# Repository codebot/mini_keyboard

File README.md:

# mini_keyboard

 * mk1: based on Cherry ML. Unfinished
 * mk2: based on Kailh 1350 low-profile "Choc"

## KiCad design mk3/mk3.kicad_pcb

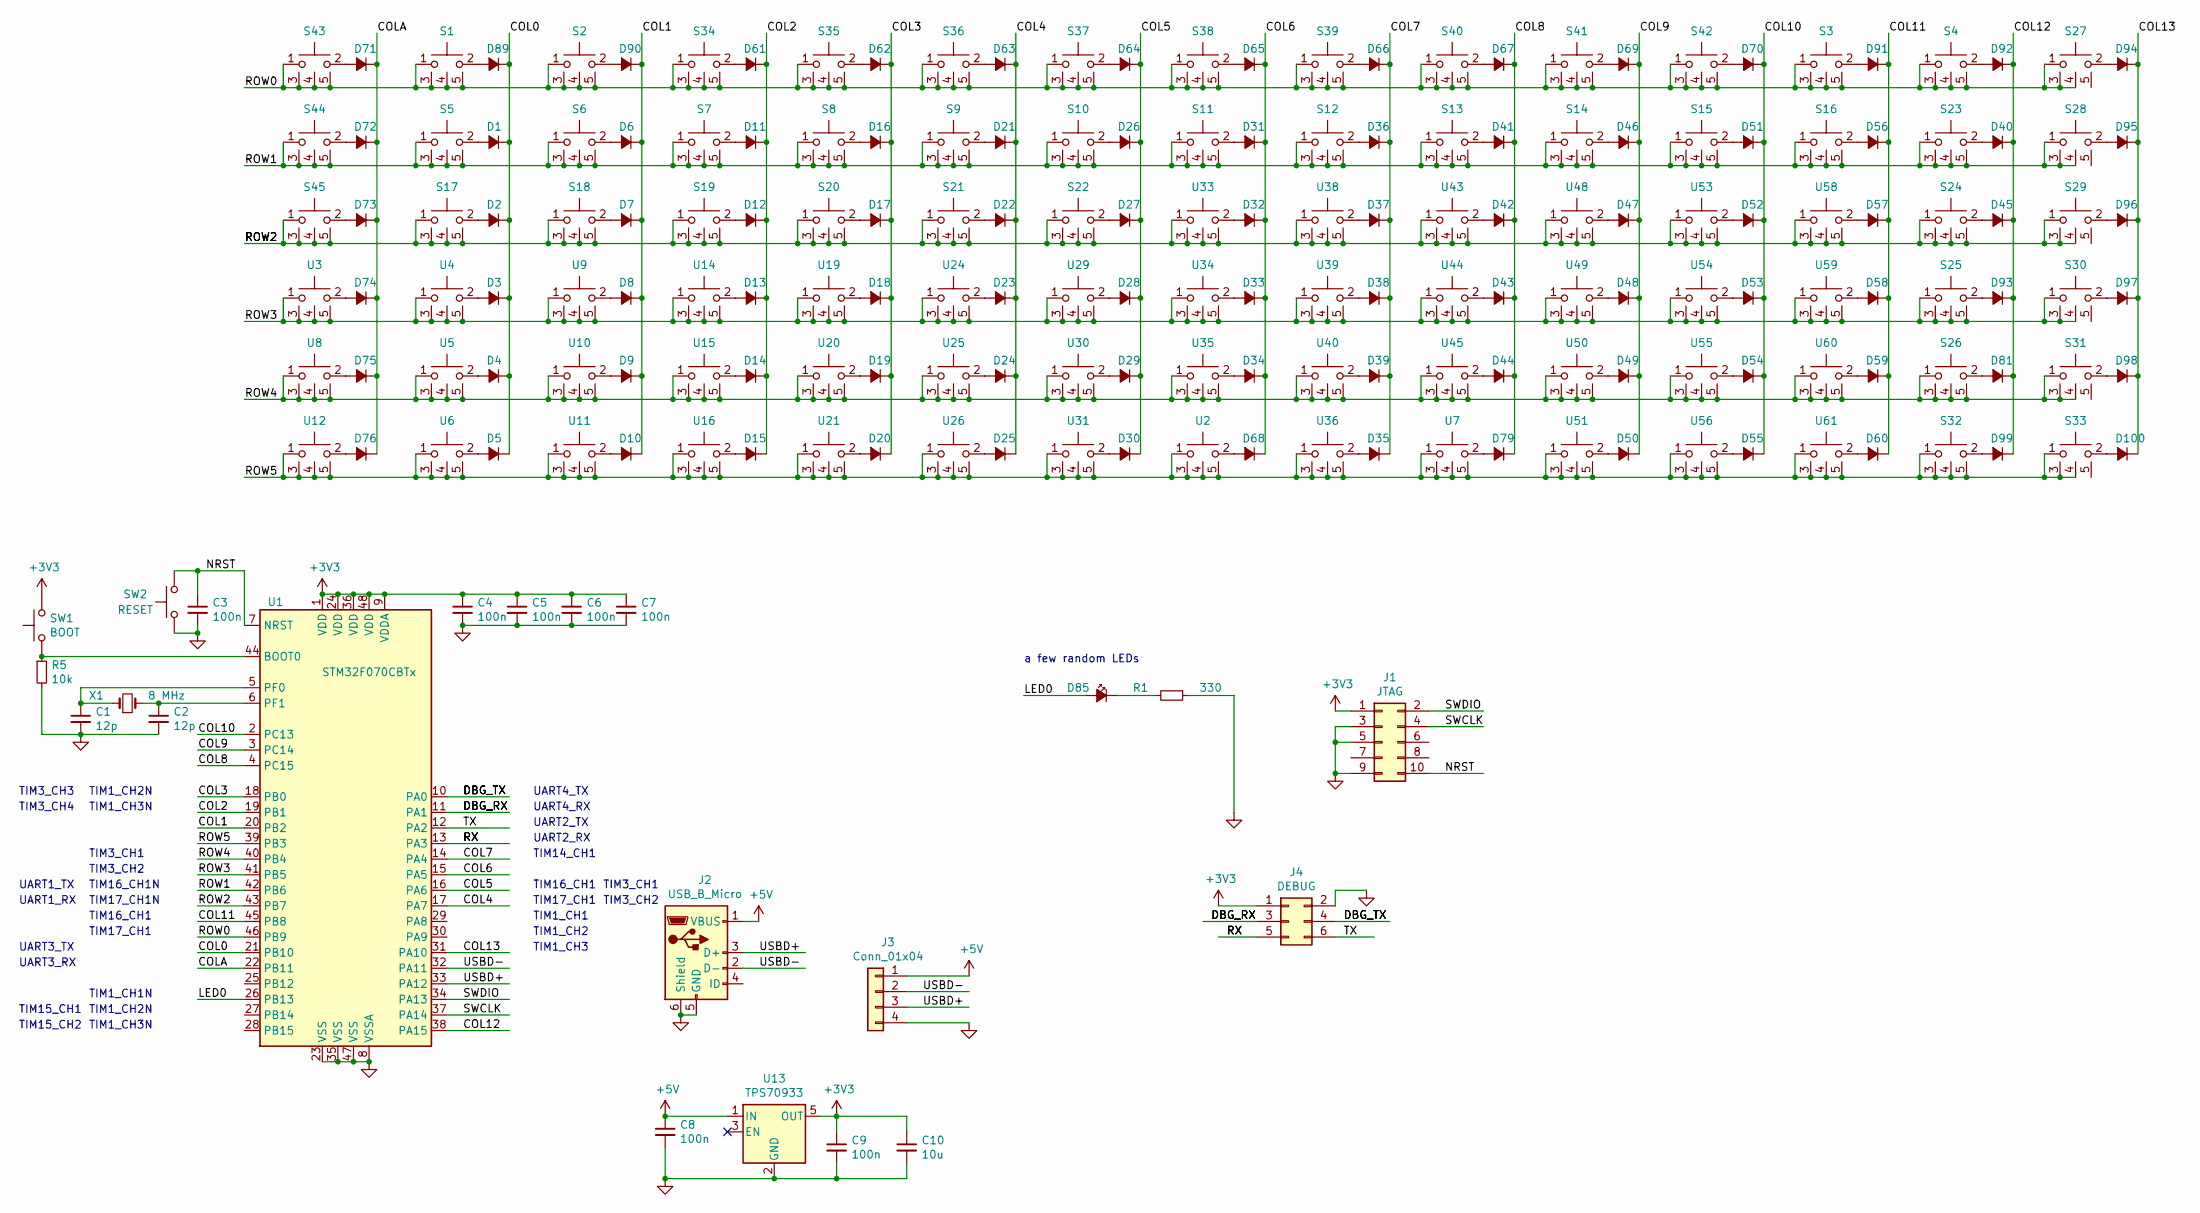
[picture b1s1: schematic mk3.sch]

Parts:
C1, C2: 12p; C_0603_1608Metric
C3, C4, C5, C6, C7, C8, C9: 100n; C_0603_1608Metric
C10: 10u; C_0805_2012Metric
D1, D2, D3, D4, D5, D6, D7, D8, D9, D10, D11, D12, D13, D14, D15, D16, D17, D18, D19, D20, D21, D22, D23, D24, D25, D26, D27, D28, D29, D30, D31, D32, D33, D34, D35, D36, D37, D38, D39, D40, D41, D42, D43, D44, D45, D46, D47, D48, D49, D50, D51, D52, D53, D54, D55, D56, D57, D58, D59, D60, D61, D62, D63, D64, D65, D66, D67, D68, D69, D70, D71, D72, D73, D74, D75, D76, D79, D81, D89, D90, D91, D92, D93, D94, D95, D96, D97, D98, D99, D100: 1N4148; D_SOD-123
D85: LED_Small_ALT; LED_D3.0mm
J1: JTAG; PinHeader_2x05_P1.27mm_Vertical
J2: USB_B_Micro; USB_Micro-B_Molex-105017-0001
J3: Conn_01x04; PinHeader_1x04_P2.54mm_Vertical
J4: DEBUG; PinHeader_2x03_P2.54mm_Vertical
R1: 330; R_0603_1608Metric
R5: 10k; R_0603_1608Metric
S1, S2, S3, S4, S5, S6, S7, S8, S9, S10, S11, S12, S13, S14, S15, S16, S17, S18, S19, S20, S21, S22, S23, S24, S25, S26, S27, S28, S29, S30, S31, S32, S33, S34, S35, S36, S37, S38, S39, S40, S41, S42, S43, S44, S45: CHERRY_ML; KAILH_1350
SW1: BOOT; SW_SPST_B3U-1000P
SW2: RESET; SW_SPST_B3U-1000P
U1: STM32F070CBTx; LQFP-48_7x7mm_P0.5mm
U2, U3, U4, U5, U6, U7, U8, U9, U10, U11, U12, U14, U15, U16, U19, U20, U21, U24, U25, U26, U29, U30, U31, U33, U34, U35, U36, U38, U39, U40, U43, U44, U45, U48, U49, U50, U51, U53, U54, U55, U56, U58, U59, U60, U61: CHERRY_ML; KAILH_1350
U13: TPS70933; SOT-23-5
X1: 8 MHz; Crystal_SMD_5032-2Pin_5.0x3.2mm

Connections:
+3V3: C4.1, C5.1, C6.1, C7.1, C9.1, C10.1, J1.1, J4.1, SW1.2, U1.1 (VDD), U1.9 (VDDA), U1.24 (VDD), U1.36 (VDD), U1.48 (VDD), U13.5 (OUT)
+5V: C8.1, J2.1 (VBUS), J3.1, U13.1 (IN)
/COL0: D1.1 (K), D2.1 (K), D3.1 (K), D4.1 (K), D5.1 (K), D89.1 (K), U1.21 (PB10)
/COL1: D6.1 (K), D7.1 (K), D8.1 (K), D9.1 (K), D10.1 (K), D90.1 (K), U1.20 (PB2)
/COL2: D11.1 (K), D12.1 (K), D13.1 (K), D14.1 (K), D15.1 (K), D61.1 (K), U1.19 (PB1)
/COL3: D16.1 (K), D17.1 (K), D18.1 (K), D19.1 (K), D20.1 (K), D62.1 (K), U1.18 (PB0)
/COL4: D21.1 (K), D22.1 (K), D23.1 (K), D24.1 (K), D25.1 (K), D63.1 (K), U1.17 (PA7)
/COL5: D26.1 (K), D27.1 (K), D28.1 (K), D29.1 (K), D30.1 (K), D64.1 (K), U1.16 (PA6)
/COL6: D31.1 (K), D32.1 (K), D33.1 (K), D34.1 (K), D65.1 (K), D68.1 (K), U1.15 (PA5)
/COL7: D35.1 (K), D36.1 (K), D37.1 (K), D38.1 (K), D39.1 (K), D66.1 (K), U1.14 (PA4)
/COL8: D41.1 (K), D42.1 (K), D43.1 (K), D44.1 (K), D67.1 (K), D79.1 (K), U1.4 (PC15)
/COL9: D46.1 (K), D47.1 (K), D48.1 (K), D49.1 (K), D50.1 (K), D69.1 (K), U1.3 (PC14)
/COL10: D51.1 (K), D52.1 (K), D53.1 (K), D54.1 (K), D55.1 (K), D70.1 (K), U1.2 (PC13)
/COL11: D56.1 (K), D57.1 (K), D58.1 (K), D59.1 (K), D60.1 (K), D91.1 (K), U1.45 (PB8)
/COL12: D40.1 (K), D45.1 (K), D81.1 (K), D92.1 (K), D93.1 (K), D99.1 (K), U1.38 (PA15)
/COL13: D94.1 (K), D95.1 (K), D96.1 (K), D97.1 (K), D98.1 (K), D100.1 (K), U1.31 (PA10)
/COLA: D71.1 (K), D72.1 (K), D73.1 (K), D74.1 (K), D75.1 (K), D76.1 (K), U1.22 (PB11)
/DBG_RX: J4.3, U1.11 (PA1)
/DBG_TX: J4.4, U1.10 (PA0)
/LED0: D85.2 (A), U1.26 (PB13)
/NRST: C3.1, J1.10, SW2.2, U1.7 (NRST)
/ROW0: S1.1, S1.3, S1.4, S1.5, S2.1, S2.3, S2.4, S2.5, S3.1, S3.3, S3.4, S3.5, S4.1, S4.3, S4.4, S4.5, S27.1, S27.3, S27.4, S34.1, S34.3, S34.4, S34.5, S35.1, S35.3, S35.4, S35.5, S36.1, S36.3, S36.4, S36.5, S37.1, S37.3, S37.4, S37.5, S38.1, S38.3, S38.4, S38.5, S39.1, S39.3, S39.4, S39.5, S40.1, S40.3, S40.4, S40.5, S41.1, S41.3, S41.4, S41.5, S42.1, S42.3, S42.4, S42.5, S43.1, S43.3, S43.4, S43.5, U1.46 (PB9)
/ROW1: S5.1, S5.3, S5.4, S5.5, S6.1, S6.3, S6.4, S6.5, S7.1, S7.3, S7.4, S7.5, S8.1, S8.3, S8.4, S8.5, S9.1, S9.3, S9.4, S9.5, S10.1, S10.3, S10.4, S10.5, S11.1, S11.3, S11.4, S11.5, S12.1, S12.3, S12.4, S12.5, S13.1, S13.3, S13.4, S13.5, S14.1, S14.3, S14.4, S14.5, S15.1, S15.3, S15.4, S15.5, S16.1, S16.3, S16.4, S16.5, S23.1, S23.3, S23.4, S23.5, S28.1, S28.3, S28.4, S44.1, S44.3, S44.4, S44.5, U1.42 (PB6)
/ROW2: S17.1, S17.3, S17.4, S17.5, S18.1, S18.3, S18.4, S18.5, S19.1, S19.3, S19.4, S19.5, S20.1, S20.3, S20.4, S20.5, S21.1, S21.3, S21.4, S21.5, S22.1, S22.3, S22.4, S22.5, S24.1, S24.3, S24.4, S24.5, S29.1, S29.3, S29.4, S45.1, S45.3, S45.4, S45.5, U1.43 (PB7), U33.1, U33.3, U33.4, U33.5, U38.1, U38.3, U38.4, U38.5, U43.1, U43.3, U43.4, U43.5, U48.1, U48.3, U48.4, U48.5, U53.1, U53.3, U53.4, U53.5, U58.1, U58.3, U58.4, U58.5
/ROW3: S25.1, S25.3, S25.4, S25.5, S30.1, S30.3, S30.4, U1.41 (PB5), U3.1, U3.3, U3.4, U3.5, U4.1, U4.3, U4.4, U4.5, U9.1, U9.3, U9.4, U9.5, U14.1, U14.3, U14.4, U14.5, U19.1, U19.3, U19.4, U19.5, U24.1, U24.3, U24.4, U24.5, U29.1, U29.3, U29.4, U29.5, U34.1, U34.3, U34.4, U34.5, U39.1, U39.3, U39.4, U39.5, U44.1, U44.3, U44.4, U44.5, U49.1, U49.3, U49.4, U49.5, U54.1, U54.3, U54.4, U54.5, U59.1, U59.3, U59.4, U59.5
/ROW4: S26.1, S26.3, S26.4, S26.5, S31.1, S31.3, S31.4, U1.40 (PB4), U5.1, U5.3, U5.4, U5.5, U8.1, U8.3, U8.4, U8.5, U10.1, U10.3, U10.4, U10.5, U15.1, U15.3, U15.4, U15.5, U20.1, U20.3, U20.4, U20.5, U25.1, U25.3, U25.4, U25.5, U30.1, U30.3, U30.4, U30.5, U35.1, U35.3, U35.4, U35.5, U40.1, U40.3, U40.4, U40.5, U45.1, U45.3, U45.4, U45.5, U50.1, U50.3, U50.4, U50.5, U55.1, U55.3, U55.4, U55.5, U60.1, U60.3, U60.4, U60.5
/ROW5: S32.1, S32.3, S32.4, S32.5, S33.1, S33.3, S33.4, U1.39 (PB3), U2.1, U2.3, U2.4, U2.5, U6.1, U6.3, U6.4, U6.5, U7.1, U7.3, U7.4, U7.5, U11.1, U11.3, U11.4, U11.5, U12.1, U12.3, U12.4, U12.5, U16.1, U16.3, U16.4, U16.5, U21.1, U21.3, U21.4, U21.5, U26.1, U26.3, U26.4, U26.5, U31.1, U31.3, U31.4, U31.5, U36.1, U36.3, U36.4, U36.5, U51.1, U51.3, U51.4, U51.5, U56.1, U56.3, U56.4, U56.5, U61.1, U61.3, U61.4, U61.5
/RX: J4.5, U1.13 (PA3)
/SWCLK: J1.4, U1.37 (PA14)
/SWDIO: J1.2, U1.34 (PA13)
/TX: J4.6, U1.12 (PA2)
/USBD+: J2.3 (D+), J3.3, U1.33 (PA12)
/USBD-: J2.2 (D-), J3.2, U1.32 (PA11)
GND: C1.2, C2.2, C3.2, C4.2, C5.2, C6.2, C7.2, C8.2, C9.2, C10.2, J1.3, J1.5, J1.9, J2.5 (GND), J2.6 (Shield), J3.4, J4.2, R1.1, R5.2, SW2.1, U1.8 (VSSA), U1.23 (VSS), U1.35 (VSS), U1.47 (VSS), U13.2 (GND)
unnamed: C1.1, U1.5 (PF0), X1.1
unnamed: C2.1, U1.6 (PF1), X1.2
unnamed: D1.2 (A), S5.2
unnamed: D2.2 (A), S17.2
unnamed: D3.2 (A), U4.2
unnamed: D4.2 (A), U5.2
unnamed: D5.2 (A), U6.2
unnamed: D6.2 (A), S6.2
unnamed: D7.2 (A), S18.2
unnamed: D8.2 (A), U9.2
unnamed: D9.2 (A), U10.2
unnamed: D10.2 (A), U11.2
unnamed: D11.2 (A), S7.2
unnamed: D12.2 (A), S19.2
unnamed: D13.2 (A), U14.2
unnamed: D14.2 (A), U15.2
unnamed: D15.2 (A), U16.2
unnamed: D16.2 (A), S8.2
unnamed: D17.2 (A), S20.2
unnamed: D18.2 (A), U19.2
unnamed: D19.2 (A), U20.2
unnamed: D20.2 (A), U21.2
unnamed: D21.2 (A), S9.2
unnamed: D22.2 (A), S21.2
unnamed: D23.2 (A), U24.2
unnamed: D24.2 (A), U25.2
unnamed: D25.2 (A), U26.2
unnamed: D26.2 (A), S10.2
unnamed: D27.2 (A), S22.2
unnamed: D28.2 (A), U29.2
unnamed: D29.2 (A), U30.2
unnamed: D30.2 (A), U31.2
unnamed: D31.2 (A), S11.2
unnamed: D32.2 (A), U33.2
unnamed: D33.2 (A), U34.2
unnamed: D34.2 (A), U35.2
unnamed: D35.2 (A), U36.2
unnamed: D36.2 (A), S12.2
unnamed: D37.2 (A), U38.2
unnamed: D38.2 (A), U39.2
unnamed: D39.2 (A), U40.2
unnamed: D40.2 (A), S23.2
unnamed: D41.2 (A), S13.2
unnamed: D42.2 (A), U43.2
unnamed: D43.2 (A), U44.2
unnamed: D44.2 (A), U45.2
unnamed: D45.2 (A), S24.2
unnamed: D46.2 (A), S14.2
unnamed: D47.2 (A), U48.2
unnamed: D48.2 (A), U49.2
unnamed: D49.2 (A), U50.2
unnamed: D50.2 (A), U51.2
unnamed: D51.2 (A), S15.2
unnamed: D52.2 (A), U53.2
unnamed: D53.2 (A), U54.2
unnamed: D54.2 (A), U55.2
unnamed: D55.2 (A), U56.2
unnamed: D56.2 (A), S16.2
unnamed: D57.2 (A), U58.2
unnamed: D58.2 (A), U59.2
unnamed: D59.2 (A), U60.2
unnamed: D60.2 (A), U61.2
unnamed: D61.2 (A), S34.2
unnamed: D62.2 (A), S35.2
unnamed: D63.2 (A), S36.2
unnamed: D64.2 (A), S37.2
unnamed: D65.2 (A), S38.2
unnamed: D66.2 (A), S39.2
unnamed: D67.2 (A), S40.2
unnamed: D68.2 (A), U2.2
unnamed: D69.2 (A), S41.2
unnamed: D70.2 (A), S42.2
unnamed: D71.2 (A), S43.2
unnamed: D72.2 (A), S44.2
unnamed: D73.2 (A), S45.2
unnamed: D74.2 (A), U3.2
unnamed: D75.2 (A), U8.2
unnamed: D76.2 (A), U12.2
unnamed: D79.2 (A), U7.2
unnamed: D81.2 (A), S26.2
unnamed: D85.1 (K), R1.2
unnamed: D89.2 (A), S1.2
unnamed: D90.2 (A), S2.2
unnamed: D91.2 (A), S3.2
unnamed: D92.2 (A), S4.2
unnamed: D93.2 (A), S25.2
unnamed: D94.2 (A), S27.2
unnamed: D95.2 (A), S28.2
unnamed: D96.2 (A), S29.2
unnamed: D97.2 (A), S30.2
unnamed: D98.2 (A), S31.2
unnamed: D99.2 (A), S32.2
unnamed: D100.2 (A), S33.2
unnamed: R5.1, SW1.1, U1.44 (BOOT0)

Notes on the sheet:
a few random LEDs
TIM14_CH1
TIM16_CH1
TIM17_CH1
TIM3_CH1
TIM3_CH2
TIM1_CH1
TIM1_CH2
TIM1_CH3
TIM1_CH2N
TIM1_CH3N
TIM3_CH3
TIM3_CH4
TIM16_CH1N
TIM17_CH1N
UART3_TX
UART3_RX
TIM1_CH1N
TIM15_CH1
TIM15_CH2
UART1_TX
UART1_RX
UART2_TX
UART2_RX
UART4_TX
UART4_RX

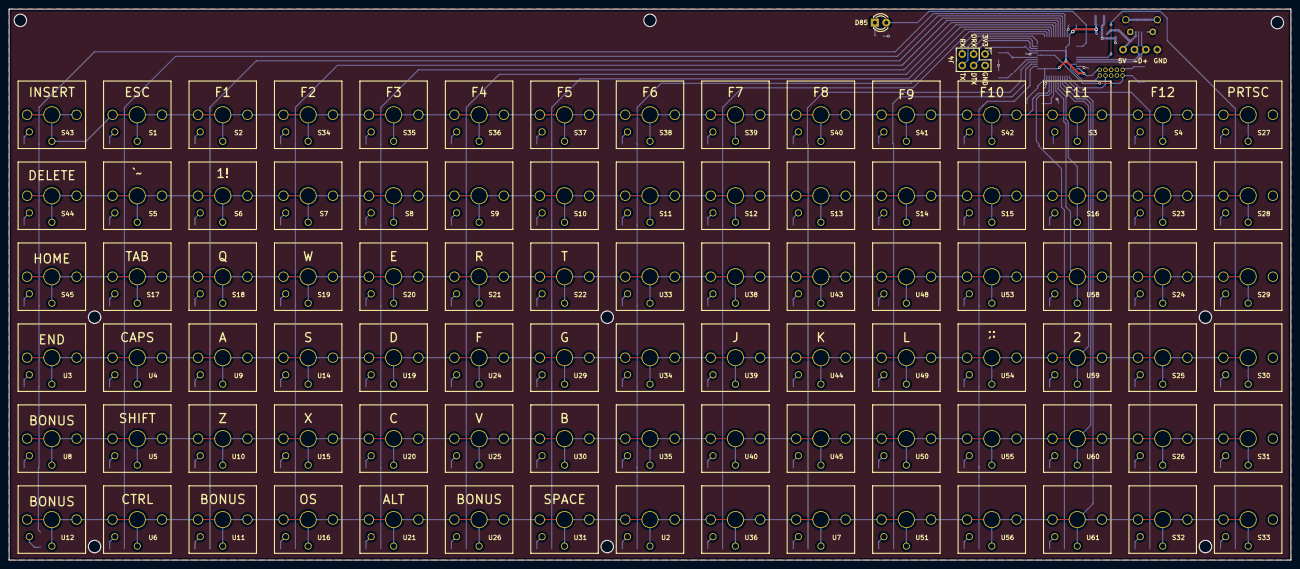
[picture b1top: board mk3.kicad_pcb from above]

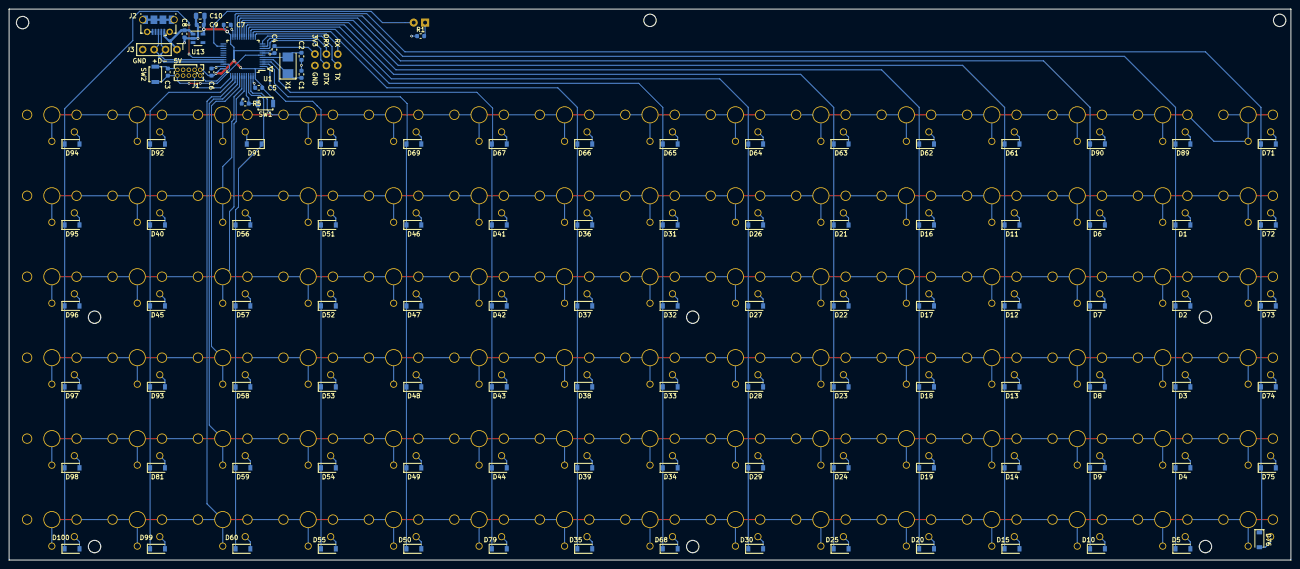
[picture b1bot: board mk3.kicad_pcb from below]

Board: 2 copper layers, 285.0 x 122.5 mm, 202 parts (110 on the bottom side), 128 nets.

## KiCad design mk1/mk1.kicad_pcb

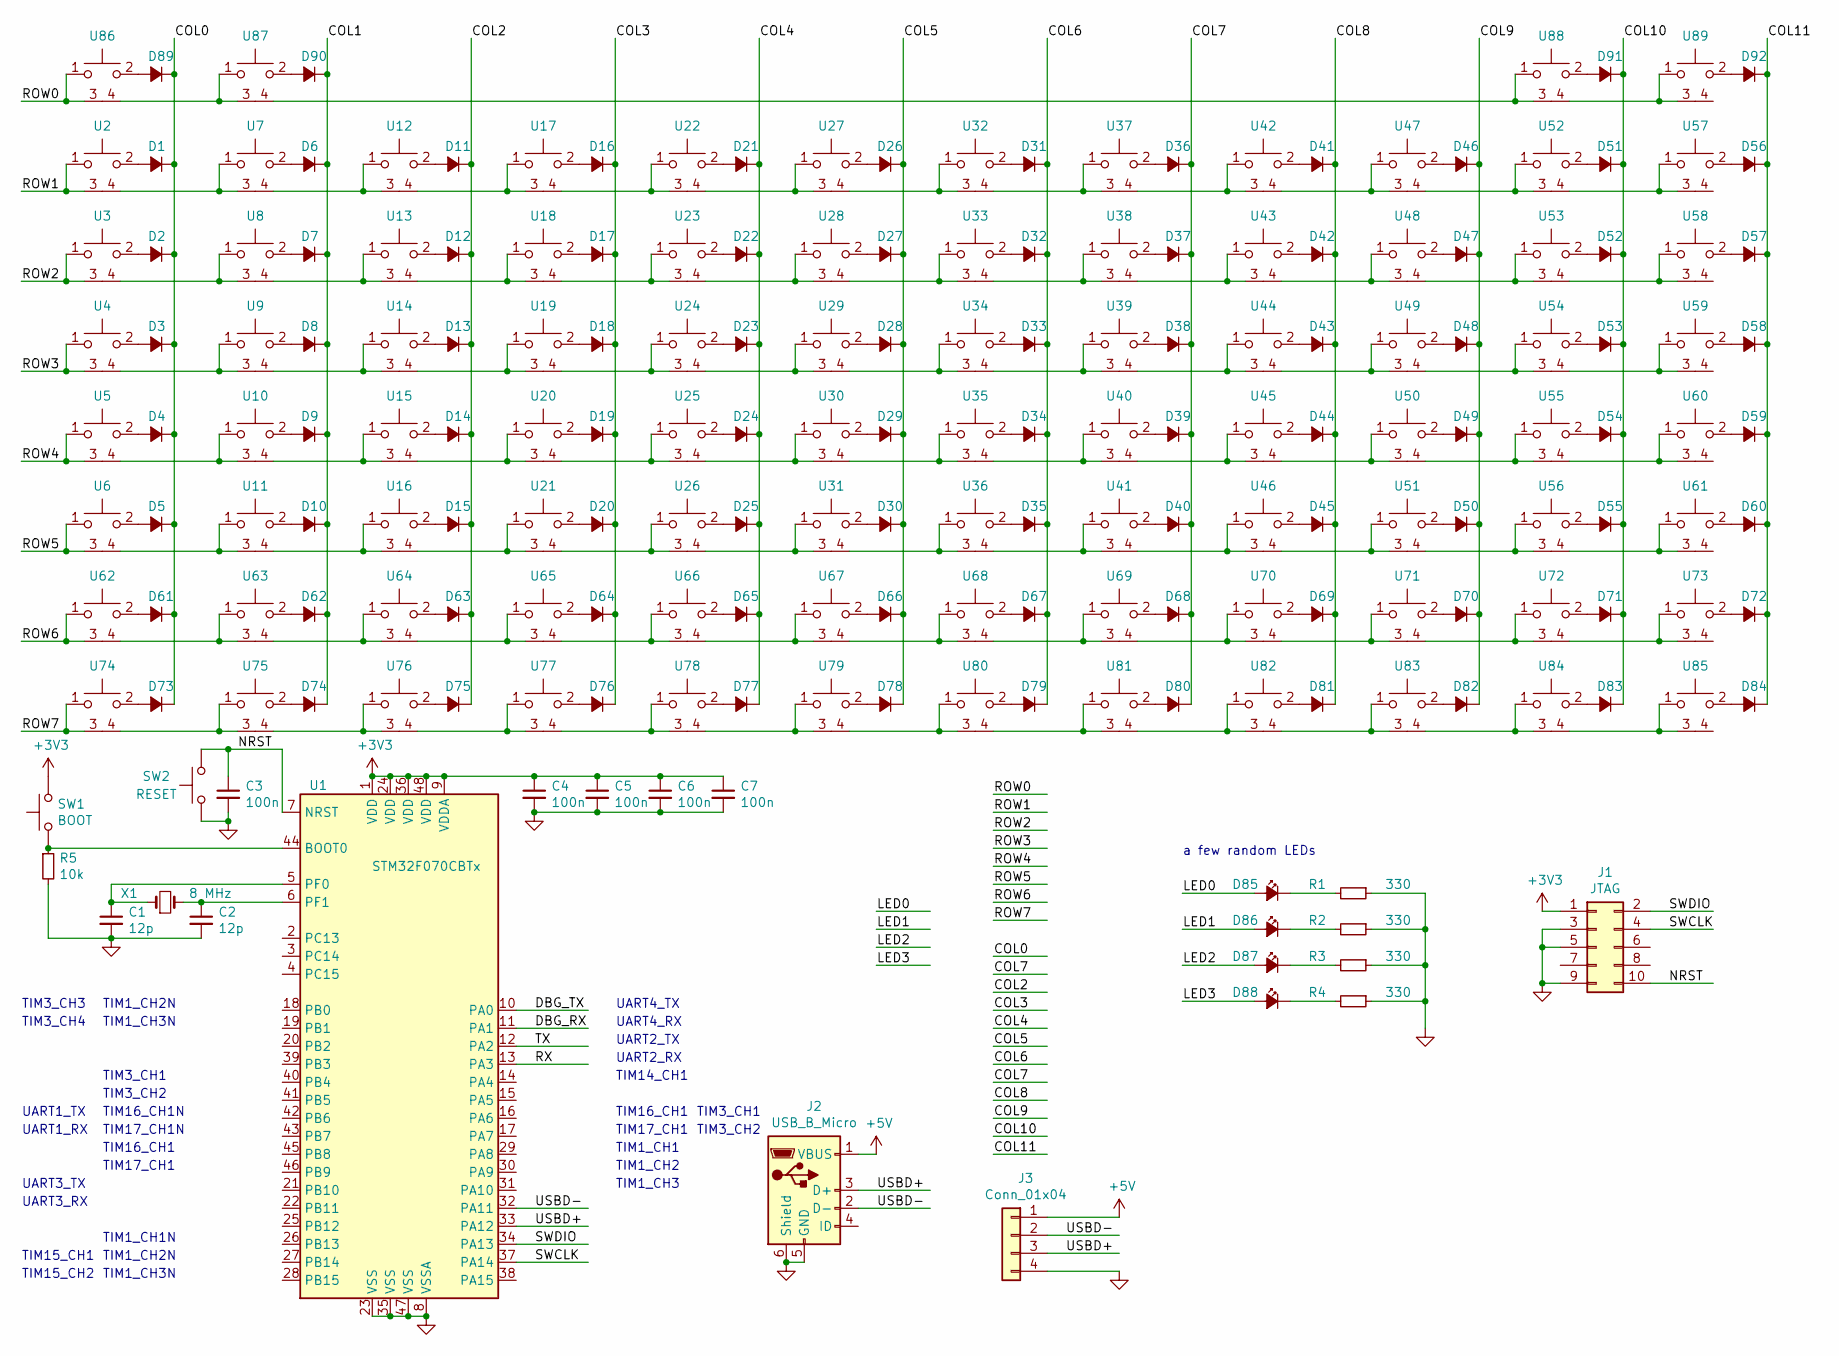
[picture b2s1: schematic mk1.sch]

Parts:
C1, C2: 12p; C_0603_1608Metric
C3, C4, C5, C6, C7: 100n; C_0603_1608Metric
D1, D2, D3, D4, D5, D6, D7, D8, D9, D10, D11, D12, D13, D14, D15, D16, D17, D18, D19, D20, D21, D22, D23, D24, D25, D26, D27, D28, D29, D30, D31, D32, D33, D34, D35, D36, D37, D38, D39, D40, D41, D42, D43, D44, D45, D46, D47, D48, D49, D50, D51, D52, D53, D54, D55, D56, D57, D58, D59, D60, D61, D62, D63, D64, D65, D66, D67, D68, D69, D70, D71, D72, D73, D74, D75, D76, D77, D78, D79, D80, D81, D82, D83, D84, D89, D90, D91, D92: 1N4148; D_SOD-123
D85, D86, D87, D88: LED_Small_ALT; LED_D3.0mm
J1: JTAG; PinHeader_2x05_P1.27mm_Vertical
J2: USB_B_Micro; USB_Micro-B_Molex-105017-0001
J3: Conn_01x04; PinHeader_1x04_P2.54mm_Vertical
R1, R2, R3, R4: 330; R_0603_1608Metric
R5: 10k; R_0603_1608Metric
SW1: BOOT; SW_SPST_B3U-1000P
SW2: RESET; SW_SPST_B3U-1000P
U1: STM32F070CBTx; LQFP-48_7x7mm_P0.5mm
U2, U3, U4, U5, U6, U7, U8, U9, U10, U11, U12, U13, U14, U15, U16, U17, U18, U19, U20, U21, U22, U23, U24, U25, U26, U27, U28, U29, U30, U31, U32, U33, U34, U35, U36, U37, U38, U39, U40, U41, U42, U43, U44, U45, U46, U47, U48, U49, U50, U51, U52, U53, U54, U55, U56, U57, U58, U59, U60, U61, U62, U63, U64, U65, U66, U67, U68, U69, U70, U71, U72, U73, U74, U75, U76, U77, U78, U79, U80, U81, U82, U83, U84, U85, U86, U87, U88, U89: CHERRY_ML
X1: 8 MHz; Crystal_SMD_5032-2Pin_5.0x3.2mm

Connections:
+3V3: C4.1, C5.1, C6.1, C7.1, J1.1, SW1.2, U1.1 (VDD), U1.9 (VDDA), U1.24 (VDD), U1.36 (VDD), U1.48 (VDD)
+5V: J2.1 (VBUS), J3.1
/COL0: D1.1 (K), D2.1 (K), D3.1 (K), D4.1 (K), D5.1 (K), D61.1 (K), D73.1 (K), D89.1 (K)
/COL1: D6.1 (K), D7.1 (K), D8.1 (K), D9.1 (K), D10.1 (K), D62.1 (K), D74.1 (K), D90.1 (K)
/COL2: D11.1 (K), D12.1 (K), D13.1 (K), D14.1 (K), D15.1 (K), D63.1 (K), D75.1 (K)
/COL3: D16.1 (K), D17.1 (K), D18.1 (K), D19.1 (K), D20.1 (K), D64.1 (K), D76.1 (K)
/COL4: D21.1 (K), D22.1 (K), D23.1 (K), D24.1 (K), D25.1 (K), D65.1 (K), D77.1 (K)
/COL5: D26.1 (K), D27.1 (K), D28.1 (K), D29.1 (K), D30.1 (K), D66.1 (K), D78.1 (K)
/COL6: D31.1 (K), D32.1 (K), D33.1 (K), D34.1 (K), D35.1 (K), D67.1 (K), D79.1 (K)
/COL7: D36.1 (K), D37.1 (K), D38.1 (K), D39.1 (K), D40.1 (K), D68.1 (K), D80.1 (K)
/COL8: D41.1 (K), D42.1 (K), D43.1 (K), D44.1 (K), D45.1 (K), D69.1 (K), D81.1 (K)
/COL9: D46.1 (K), D47.1 (K), D48.1 (K), D49.1 (K), D50.1 (K), D70.1 (K), D82.1 (K)
/COL10: D51.1 (K), D52.1 (K), D53.1 (K), D54.1 (K), D55.1 (K), D71.1 (K), D83.1 (K), D91.1 (K)
/COL11: D56.1 (K), D57.1 (K), D58.1 (K), D59.1 (K), D60.1 (K), D72.1 (K), D84.1 (K), D92.1 (K)
/DBG_RX: U1.11 (PA1)
/DBG_TX: U1.10 (PA0)
/LED0: D85.2 (A)
/LED1: D86.2 (A)
/LED2: D87.2 (A)
/LED3: D88.2 (A)
/NRST: C3.1, J1.10, SW2.2, U1.7 (NRST)
/ROW0: U86.1, U86.3
/ROW1: U2.1, U2.3
/ROW2: U3.1, U3.3
/ROW3: U4.1, U4.3
/ROW4: U5.1, U5.3
/ROW5: U6.1, U6.3
/ROW6: U62.1, U62.3
/ROW7: U74.1, U74.3
/RX: U1.13 (PA3)
/SWCLK: J1.4, U1.37 (PA14)
/SWDIO: J1.2, U1.34 (PA13)
/TX: U1.12 (PA2)
/USBD+: J2.3 (D+), J3.3, U1.33 (PA12)
/USBD-: J2.2 (D-), J3.2, U1.32 (PA11)
GND: C1.2, C2.2, C3.2, C4.2, C5.2, C6.2, C7.2, J1.3, J1.5, J1.9, J2.5 (GND), J2.6 (Shield), J3.4, R1.1, R2.1, R3.1, R4.1, R5.2, SW2.1, U1.8 (VSSA), U1.23 (VSS), U1.35 (VSS), U1.47 (VSS)
unnamed: C1.1, U1.5 (PF0), X1.1
unnamed: C2.1, U1.6 (PF1), X1.2
unnamed: D1.2 (A), U2.2
unnamed: D2.2 (A), U3.2
unnamed: D3.2 (A), U4.2
unnamed: D4.2 (A), U5.2
unnamed: D5.2 (A), U6.2
unnamed: D6.2 (A), U7.2
unnamed: D7.2 (A), U8.2
unnamed: D8.2 (A), U9.2
unnamed: D9.2 (A), U10.2
unnamed: D10.2 (A), U11.2
unnamed: D11.2 (A), U12.2
unnamed: D12.2 (A), U13.2
unnamed: D13.2 (A), U14.2
unnamed: D14.2 (A), U15.2
unnamed: D15.2 (A), U16.2
unnamed: D16.2 (A), U17.2
unnamed: D17.2 (A), U18.2
unnamed: D18.2 (A), U19.2
unnamed: D19.2 (A), U20.2
unnamed: D20.2 (A), U21.2
unnamed: D21.2 (A), U22.2
unnamed: D22.2 (A), U23.2
unnamed: D23.2 (A), U24.2
unnamed: D24.2 (A), U25.2
unnamed: D25.2 (A), U26.2
unnamed: D26.2 (A), U27.2
unnamed: D27.2 (A), U28.2
unnamed: D28.2 (A), U29.2
unnamed: D29.2 (A), U30.2
unnamed: D30.2 (A), U31.2
unnamed: D31.2 (A), U32.2
unnamed: D32.2 (A), U33.2
unnamed: D33.2 (A), U34.2
unnamed: D34.2 (A), U35.2
unnamed: D35.2 (A), U36.2
unnamed: D36.2 (A), U37.2
unnamed: D37.2 (A), U38.2
unnamed: D38.2 (A), U39.2
unnamed: D39.2 (A), U40.2
unnamed: D40.2 (A), U41.2
unnamed: D41.2 (A), U42.2
unnamed: D42.2 (A), U43.2
unnamed: D43.2 (A), U44.2
unnamed: D44.2 (A), U45.2
unnamed: D45.2 (A), U46.2
unnamed: D46.2 (A), U47.2
unnamed: D47.2 (A), U48.2
unnamed: D48.2 (A), U49.2
unnamed: D49.2 (A), U50.2
unnamed: D50.2 (A), U51.2
unnamed: D51.2 (A), U52.2
unnamed: D52.2 (A), U53.2
unnamed: D53.2 (A), U54.2
unnamed: D54.2 (A), U55.2
unnamed: D55.2 (A), U56.2
unnamed: D56.2 (A), U57.2
unnamed: D57.2 (A), U58.2
unnamed: D58.2 (A), U59.2
unnamed: D59.2 (A), U60.2
unnamed: D60.2 (A), U61.2
unnamed: D61.2 (A), U62.2
unnamed: D62.2 (A), U63.2
unnamed: D63.2 (A), U64.2
unnamed: D64.2 (A), U65.2
unnamed: D65.2 (A), U66.2
unnamed: D66.2 (A), U67.2
unnamed: D67.2 (A), U68.2
unnamed: D68.2 (A), U69.2
unnamed: D69.2 (A), U70.2
unnamed: D70.2 (A), U71.2
unnamed: D71.2 (A), U72.2
unnamed: D72.2 (A), U73.2
unnamed: D73.2 (A), U74.2
unnamed: D74.2 (A), U75.2
unnamed: D75.2 (A), U76.2
unnamed: D76.2 (A), U77.2
unnamed: D77.2 (A), U78.2
unnamed: D78.2 (A), U79.2
unnamed: D79.2 (A), U80.2
unnamed: D80.2 (A), U81.2
unnamed: D81.2 (A), U82.2
unnamed: D82.2 (A), U83.2
unnamed: D83.2 (A), U84.2
unnamed: D84.2 (A), U85.2
unnamed: D85.1 (K), R1.2
unnamed: D86.1 (K), R2.2
unnamed: D87.1 (K), R3.2
unnamed: D88.1 (K), R4.2
unnamed: D89.2 (A), U86.2
unnamed: D90.2 (A), U87.2
unnamed: D91.2 (A), U88.2
unnamed: D92.2 (A), U89.2
unnamed: R5.1, SW1.1, U1.44 (BOOT0)
unnamed: U2.4, U7.1, U7.3
unnamed: U3.4, U8.1, U8.3
unnamed: U4.4, U9.1, U9.3
unnamed: U5.4, U10.1, U10.3
unnamed: U10.4, U15.1, U15.3
unnamed: U6.4, U11.1, U11.3
unnamed: U11.4, U16.1, U16.3
unnamed: U7.4, U12.1, U12.3
unnamed: U12.4, U17.1, U17.3
unnamed: U8.4, U13.1, U13.3
unnamed: U13.4, U18.1, U18.3
unnamed: U9.4, U14.1, U14.3
unnamed: U14.4, U19.1, U19.3
unnamed: U15.4, U20.1, U20.3
unnamed: U16.4, U21.1, U21.3
unnamed: U17.4, U22.1, U22.3
unnamed: U18.4, U23.1, U23.3
unnamed: U19.4, U24.1, U24.3
unnamed: U20.4, U25.1, U25.3
unnamed: U21.4, U26.1, U26.3
unnamed: U22.4, U27.1, U27.3
unnamed: U23.4, U28.1, U28.3
unnamed: U24.4, U29.1, U29.3
unnamed: U25.4, U30.1, U30.3
unnamed: U26.4, U31.1, U31.3
unnamed: U27.4, U32.1, U32.3
unnamed: U28.4, U33.1, U33.3
unnamed: U29.4, U34.1, U34.3
unnamed: U30.4, U35.1, U35.3
unnamed: U31.4, U36.1, U36.3
unnamed: U32.4, U37.1, U37.3
unnamed: U33.4, U38.1, U38.3
unnamed: U34.4, U39.1, U39.3
unnamed: U35.4, U40.1, U40.3
unnamed: U36.4, U41.1, U41.3
unnamed: U37.4, U42.1, U42.3
unnamed: U38.4, U43.1, U43.3
unnamed: U39.4, U44.1, U44.3
unnamed: U40.4, U45.1, U45.3
unnamed: U41.4, U46.1, U46.3
unnamed: U42.4, U47.1, U47.3
unnamed: U43.4, U48.1, U48.3
unnamed: U44.4, U49.1, U49.3
unnamed: U45.4, U50.1, U50.3
unnamed: U46.4, U51.1, U51.3
unnamed: U47.4, U52.1, U52.3
unnamed: U48.4, U53.1, U53.3
unnamed: U49.4, U54.1, U54.3
unnamed: U50.4, U55.1, U55.3
unnamed: U51.4, U56.1, U56.3
unnamed: U52.4, U57.1, U57.3
unnamed: U53.4, U58.1, U58.3
unnamed: U54.4, U59.1, U59.3
unnamed: U55.4, U60.1, U60.3
unnamed: U56.4, U61.1, U61.3
unnamed: U62.4, U63.1, U63.3
unnamed: U63.4, U64.1, U64.3
unnamed: U64.4, U65.1, U65.3
unnamed: U65.4, U66.1, U66.3
unnamed: U66.4, U67.1, U67.3
unnamed: U67.4, U68.1, U68.3
unnamed: U68.4, U69.1, U69.3
unnamed: U69.4, U70.1, U70.3
unnamed: U70.4, U71.1, U71.3
unnamed: U71.4, U72.1, U72.3
unnamed: U72.4, U73.1, U73.3
unnamed: U74.4, U75.1, U75.3
unnamed: U75.4, U76.1, U76.3
unnamed: U76.4, U77.1, U77.3
unnamed: U77.4, U78.1, U78.3
unnamed: U78.4, U79.1, U79.3
unnamed: U79.4, U80.1, U80.3
unnamed: U80.4, U81.1, U81.3
unnamed: U81.4, U82.1, U82.3
unnamed: U82.4, U83.1, U83.3
unnamed: U83.4, U84.1, U84.3
unnamed: U84.4, U85.1, U85.3
unnamed: U86.4, U87.1, U87.3
unnamed: U87.4, U88.1, U88.3
unnamed: U88.4, U89.1, U89.3

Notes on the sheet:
a few random LEDs
TIM14_CH1
TIM16_CH1
TIM17_CH1
TIM3_CH1
TIM3_CH2
TIM1_CH1
TIM1_CH2
TIM1_CH3
TIM1_CH2N
TIM1_CH3N
TIM3_CH3
TIM3_CH4
TIM16_CH1N
TIM17_CH1N
UART3_TX
UART3_RX
TIM1_CH1N
TIM15_CH1
TIM15_CH2
UART1_TX
UART1_RX
UART2_TX
UART2_RX
UART4_TX
UART4_RX

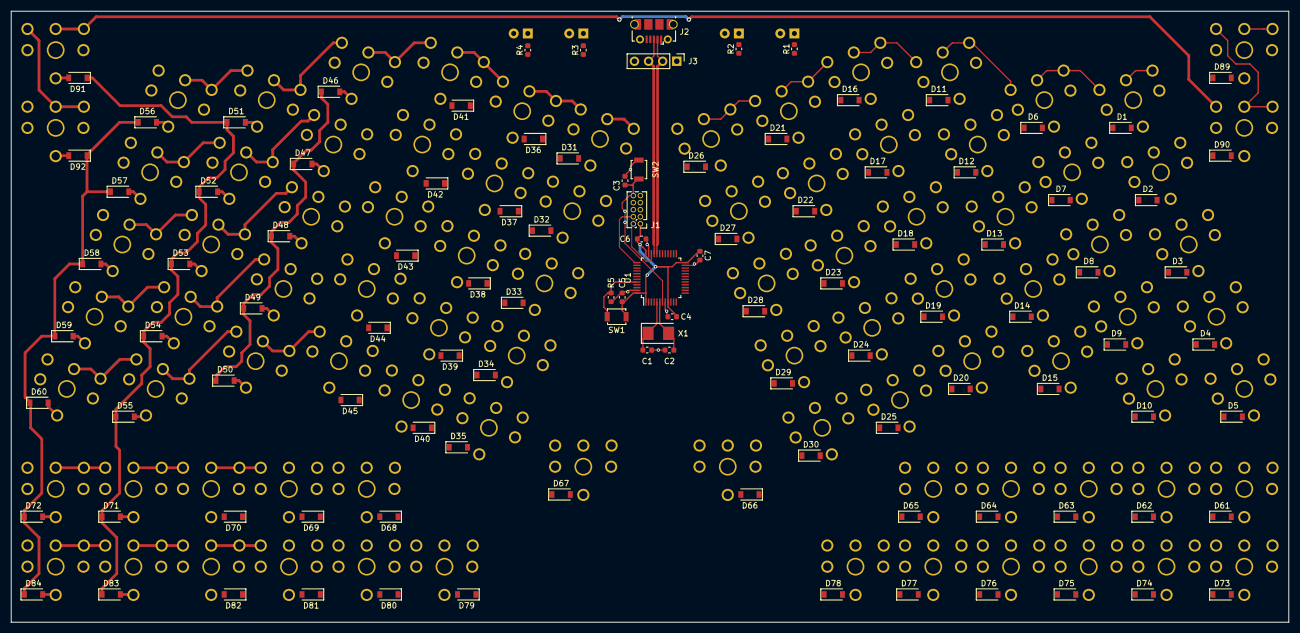
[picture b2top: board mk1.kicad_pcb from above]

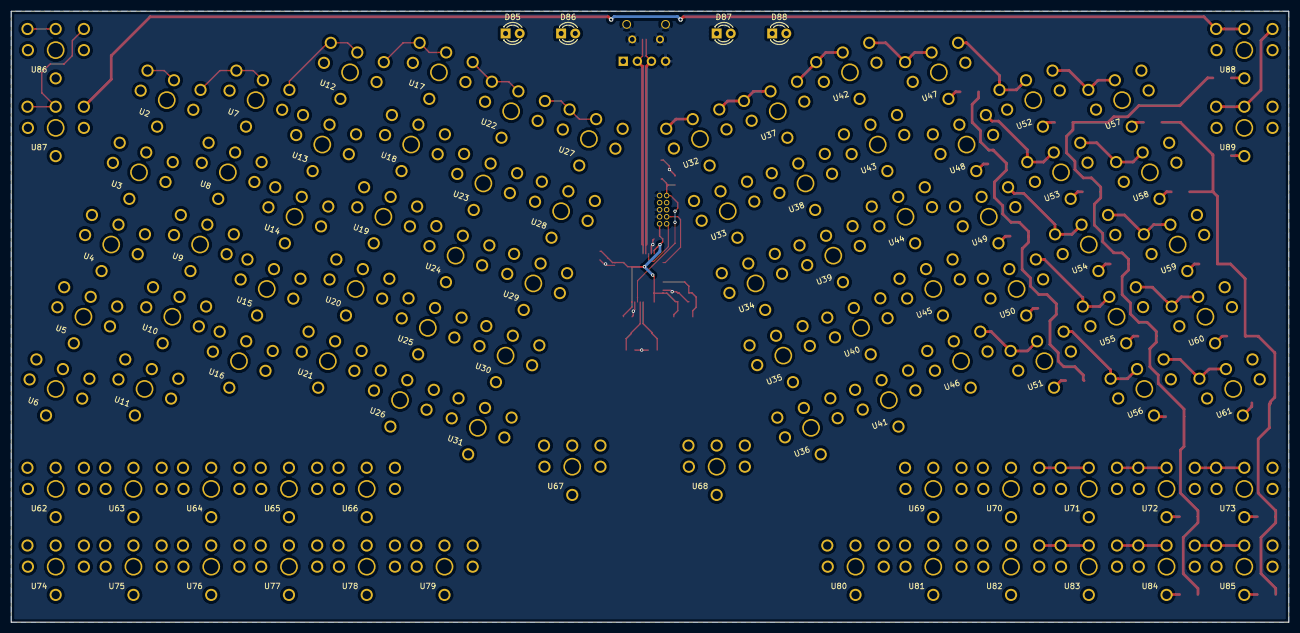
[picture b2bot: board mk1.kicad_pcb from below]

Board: 2 copper layers, 230.0 x 110.0 mm, 199 parts (92 on the bottom side), 203 nets.

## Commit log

2018-09-28 first schematic sketch
2018-09-28 using ML switch built i jumper bar
2018-09-29 more keys
2018-09-30 add mcu pin peripheral labels
2018-10-01 route a few columns
2018-10-13 mk2 using kailh choc
2018-10-16 mk3 ortho layout
2018-10-16 add another key column to left side of layout
2018-10-22 route a few columns of keys
2018-10-29 place/route keyswitches and diodes
2018-10-29 start routing columns
2018-10-31 a bit of place/route for the MCU section
2018-11-12 finish first attempt at place and route
2018-11-24 cleanup
